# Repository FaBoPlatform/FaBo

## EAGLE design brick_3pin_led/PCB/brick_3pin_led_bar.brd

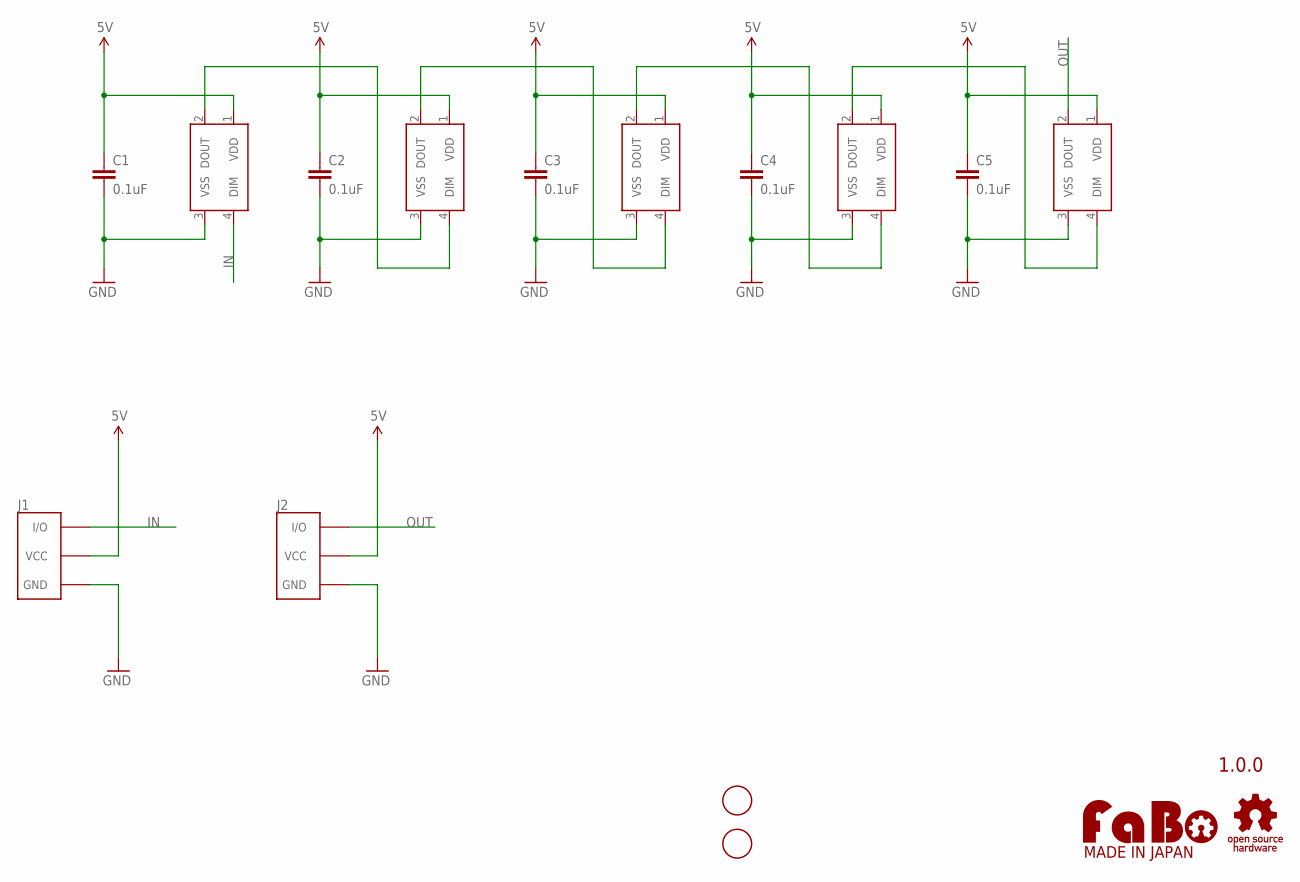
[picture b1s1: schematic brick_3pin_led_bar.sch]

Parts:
C1, C2, C3, C4, C5: 0.1uF; EIA0603
J1, J2: FABO_BRICK_3PIN-CONNECTOR; FABO_BRICK_3PIN_CONNECTOR
LED1, LED2, LED3, LED4, LED5: WS2818B
U$2, U$3: SCREW-PAD-3MM; SCREWPAD_3MM
U$4: LOGO_FABO-S_BOTTOM; LOGO_FABO_S_BOTTOM
U$5: LOGO_OSHW-M_BOTTOM; LOGO_OSHW_M_BOTTOM

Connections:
5V: C1.1, C2.1, C3.1, C4.1, C5.1, J1.VCC, J2.VCC, LED1.1 (VDD), LED2.1 (VDD), LED3.1 (VDD), LED4.1 (VDD), LED5.1 (VDD)
GND: C1.2, C2.2, C3.2, C4.2, C5.2, J1.GND, J2.GND, LED1.3 (VSS), LED2.3 (VSS), LED3.3 (VSS), LED4.3 (VSS), LED5.3 (VSS)
IN: J1.IN/OUT (I/O), LED1.4 (DIM)
unnamed: LED2.2 (DOUT), LED3.4 (DIM)
unnamed: LED3.2 (DOUT), LED4.4 (DIM)
unnamed: LED1.2 (DOUT), LED2.4 (DIM)
unnamed: LED4.2 (DOUT), LED5.4 (DIM)
OUT: J2.IN/OUT (I/O), LED5.2 (DOUT)

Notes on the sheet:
1.0.0

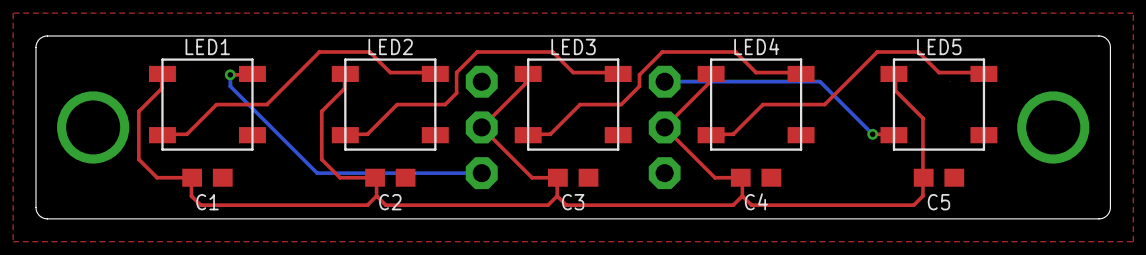
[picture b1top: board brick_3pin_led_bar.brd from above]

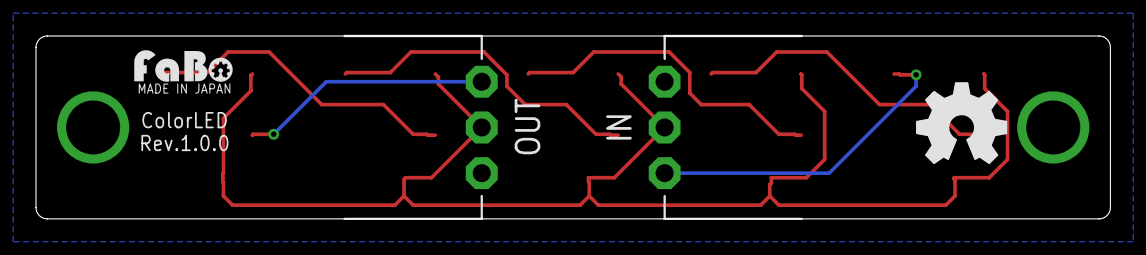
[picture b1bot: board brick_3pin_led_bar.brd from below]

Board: 2 copper layers, 59.7 x 10.2 mm, 16 parts (2 on the bottom side), 8 nets.

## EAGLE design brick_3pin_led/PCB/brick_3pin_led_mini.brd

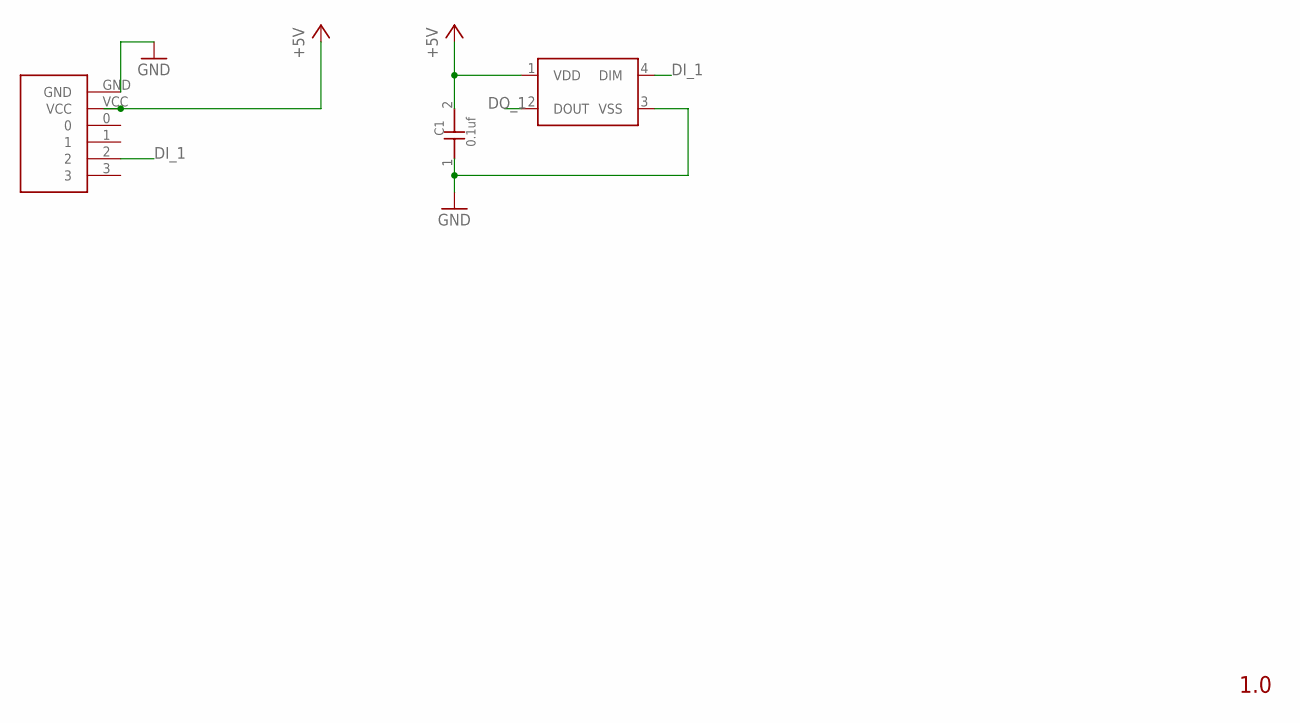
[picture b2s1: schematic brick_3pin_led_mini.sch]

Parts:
C1: 0.1uf; 0603
LED1: WS2818B
U$2: FABO-NANO

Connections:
+5V: C1.2, LED1.1 (VDD), U$2.VCC
DI_1: LED1.4 (DIM), U$2.2
DO_1: LED1.2 (DOUT)
GND: C1.1, LED1.3 (VSS), U$2.GND

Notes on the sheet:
1.0

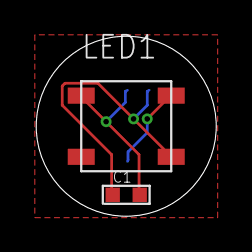
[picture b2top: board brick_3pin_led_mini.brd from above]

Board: 2 copper layers, 10.0 x 10.0 mm, 3 parts (0 on the bottom side), 3 nets.

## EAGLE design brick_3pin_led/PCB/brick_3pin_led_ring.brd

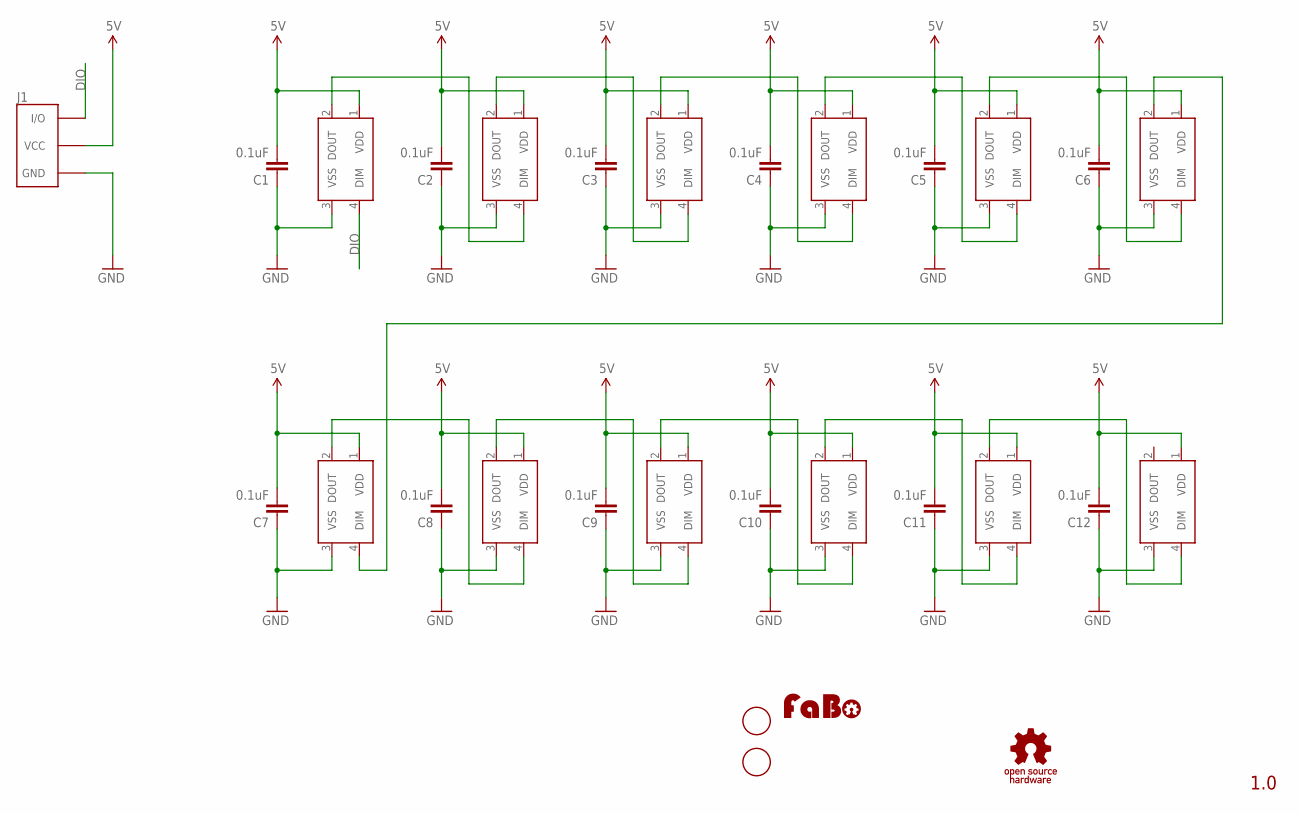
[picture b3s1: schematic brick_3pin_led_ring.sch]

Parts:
C1, C2, C3, C4, C5, C6, C7, C8, C9, C10, C11, C12: 0.1uF; EIA0603
J1: BRICK_3PIN_CONNECTOR
U$2, U$3, U$4, U$5, U$6, U$7, U$8, U$9, U$10, U$11, U$12, U$13: WS2818B
U$14: LOGO_FABO-M; LOGO_FABO_M
U$15: LOGO_OSHW_T-M; LOGO_OSHW_T_M
U$16, U$17: SCREW-PAD-3MM; SCREWPAD_3MM

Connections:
5V: C1.2, C2.2, C3.2, C4.2, C5.2, C6.2, C7.2, C8.2, C9.2, C10.2, C11.2, C12.2, J1.VCC, U$2.1 (VDD), U$3.1 (VDD), U$4.1 (VDD), U$5.1 (VDD), U$6.1 (VDD), U$7.1 (VDD), U$8.1 (VDD), U$9.1 (VDD), U$10.1 (VDD), U$11.1 (VDD), U$12.1 (VDD), U$13.1 (VDD)
DIO: J1.IN/OUT (I/O), U$2.4 (DIM)
GND: C1.1, C2.1, C3.1, C4.1, C5.1, C6.1, C7.1, C8.1, C9.1, C10.1, C11.1, C12.1, J1.GND, U$2.3 (VSS), U$3.3 (VSS), U$4.3 (VSS), U$5.3 (VSS), U$6.3 (VSS), U$7.3 (VSS), U$8.3 (VSS), U$9.3 (VSS), U$10.3 (VSS), U$11.3 (VSS), U$12.3 (VSS), U$13.3 (VSS)
unnamed: U$2.2 (DOUT), U$3.4 (DIM)
unnamed: U$3.2 (DOUT), U$4.4 (DIM)
unnamed: U$4.2 (DOUT), U$5.4 (DIM)
unnamed: U$5.2 (DOUT), U$6.4 (DIM)
unnamed: U$6.2 (DOUT), U$7.4 (DIM)
unnamed: U$7.2 (DOUT), U$8.4 (DIM)
unnamed: U$8.2 (DOUT), U$9.4 (DIM)
unnamed: U$9.2 (DOUT), U$10.4 (DIM)
unnamed: U$10.2 (DOUT), U$11.4 (DIM)
unnamed: U$11.2 (DOUT), U$12.4 (DIM)
unnamed: U$12.2 (DOUT), U$13.4 (DIM)

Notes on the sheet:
1.0

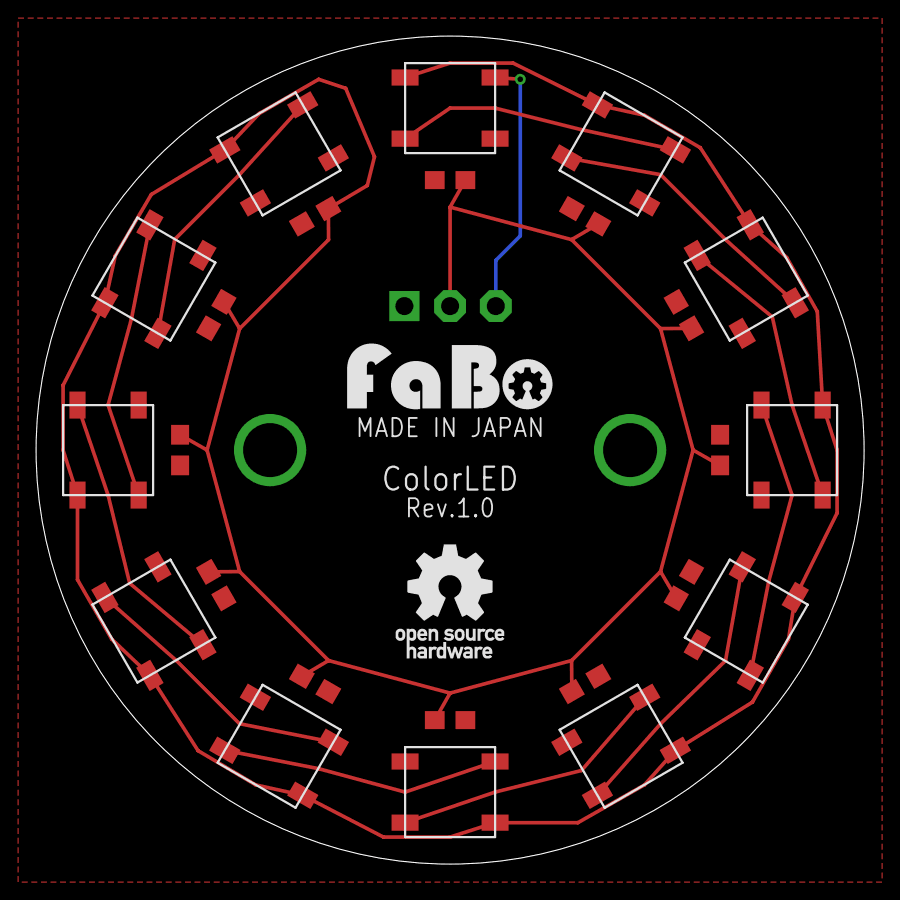
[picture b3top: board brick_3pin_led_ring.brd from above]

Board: 2 copper layers, 46.0 x 46.0 mm, 29 parts (1 on the bottom side), 14 nets.

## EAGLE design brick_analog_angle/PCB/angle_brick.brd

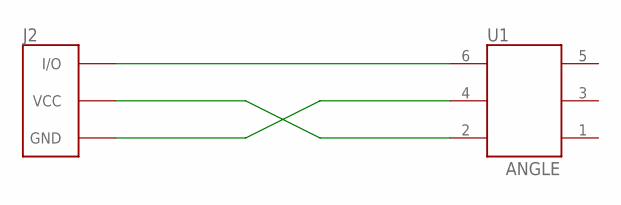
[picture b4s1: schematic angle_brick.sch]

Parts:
J2: BRICK_3PIN
U1: ANGLE; ROTARYENCORDER_BRICK

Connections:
GND: J2.GND, U1.4
unnamed: J2.IN/OUT (I/O), U1.6
VCC: J2.VCC, U1.2

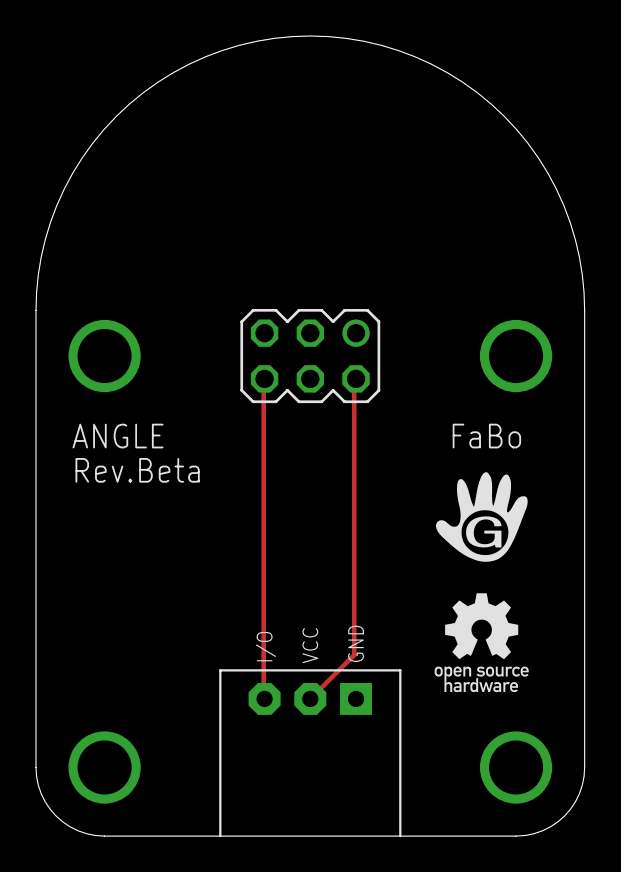
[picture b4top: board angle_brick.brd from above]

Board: 2 copper layers, 30.5 x 44.5 mm, 4 parts (0 on the bottom side), 3 nets.

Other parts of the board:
U$2: LOGO_OSHW_T_M
U$4: LOGO_GCLUE_M

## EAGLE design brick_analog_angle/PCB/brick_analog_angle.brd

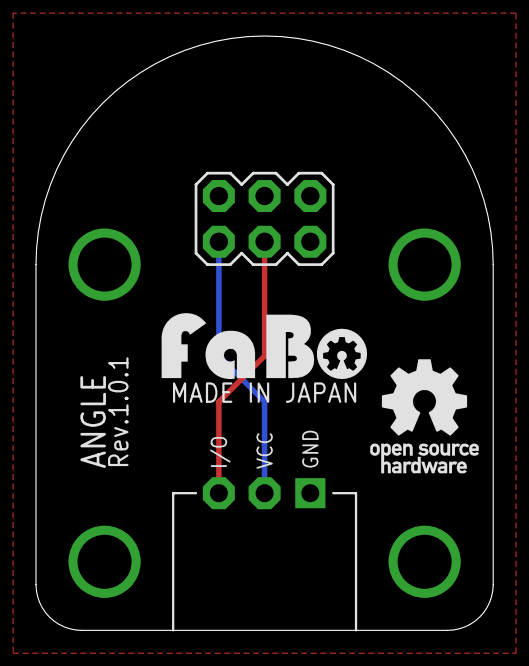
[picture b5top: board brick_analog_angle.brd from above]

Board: 2 copper layers, 25.4 x 33.0 mm, 4 parts (0 on the bottom side), 3 nets.

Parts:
J1: FABO_BRICK_3PIN
U1: ANGLE; ROTARYENCORDER_BRICK
U$2: LOGO_FABO_M
U$3: LOGO_OSHW_T_M

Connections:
GND: J1.GND, U1.5
unnamed: J1.IN/OUT, U1.3
VCC: J1.VCC, U1.1

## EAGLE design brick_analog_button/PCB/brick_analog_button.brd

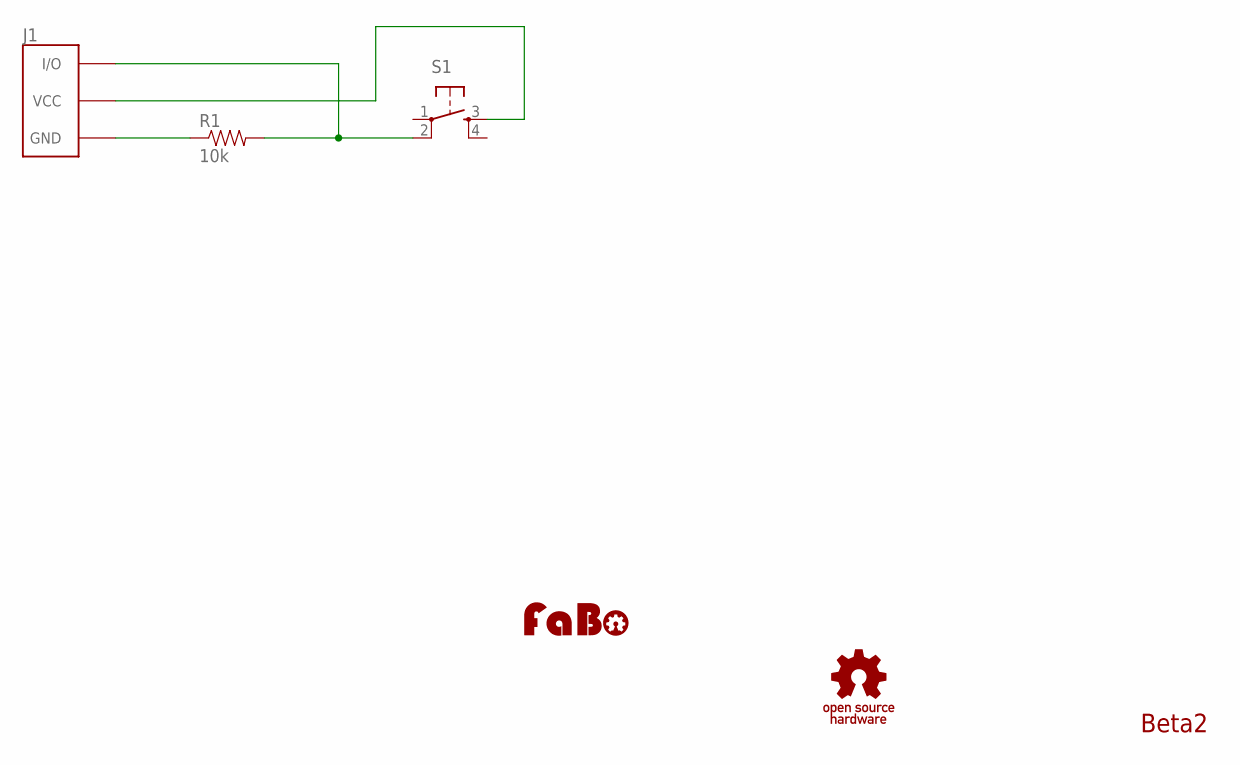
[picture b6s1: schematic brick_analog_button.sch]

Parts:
J1: BRICK_3PIN
R1: 10k; RES-AXL-REGULAR
S1: SWITCH-TACT-6MM; DTS_6_V
U$2: LOGO_FABO-M; LOGO_FABO_M
U$3: LOGO_OSHW_T-M; LOGO_OSHW_T_M

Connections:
GND: J1.GND, R1.P$1 (1)
unnamed: J1.VCC, S1.3
unnamed: J1.IN/OUT (I/O), R1.P$2 (2), S1.2

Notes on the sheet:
Beta2

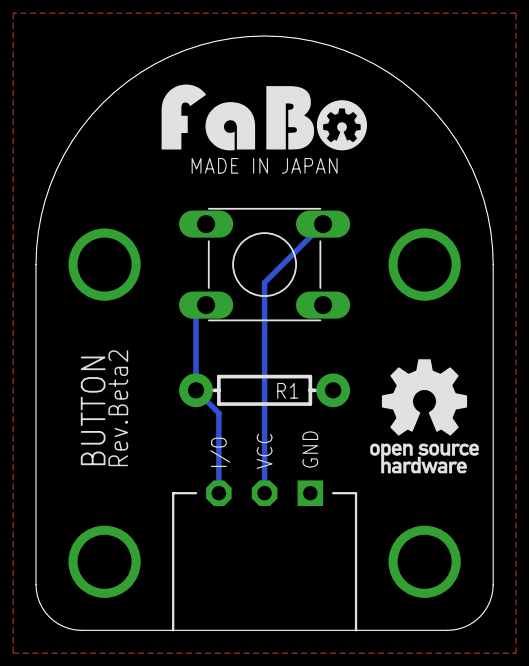
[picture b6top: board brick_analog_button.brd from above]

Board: 2 copper layers, 25.4 x 33.0 mm, 5 parts (0 on the bottom side), 3 nets.

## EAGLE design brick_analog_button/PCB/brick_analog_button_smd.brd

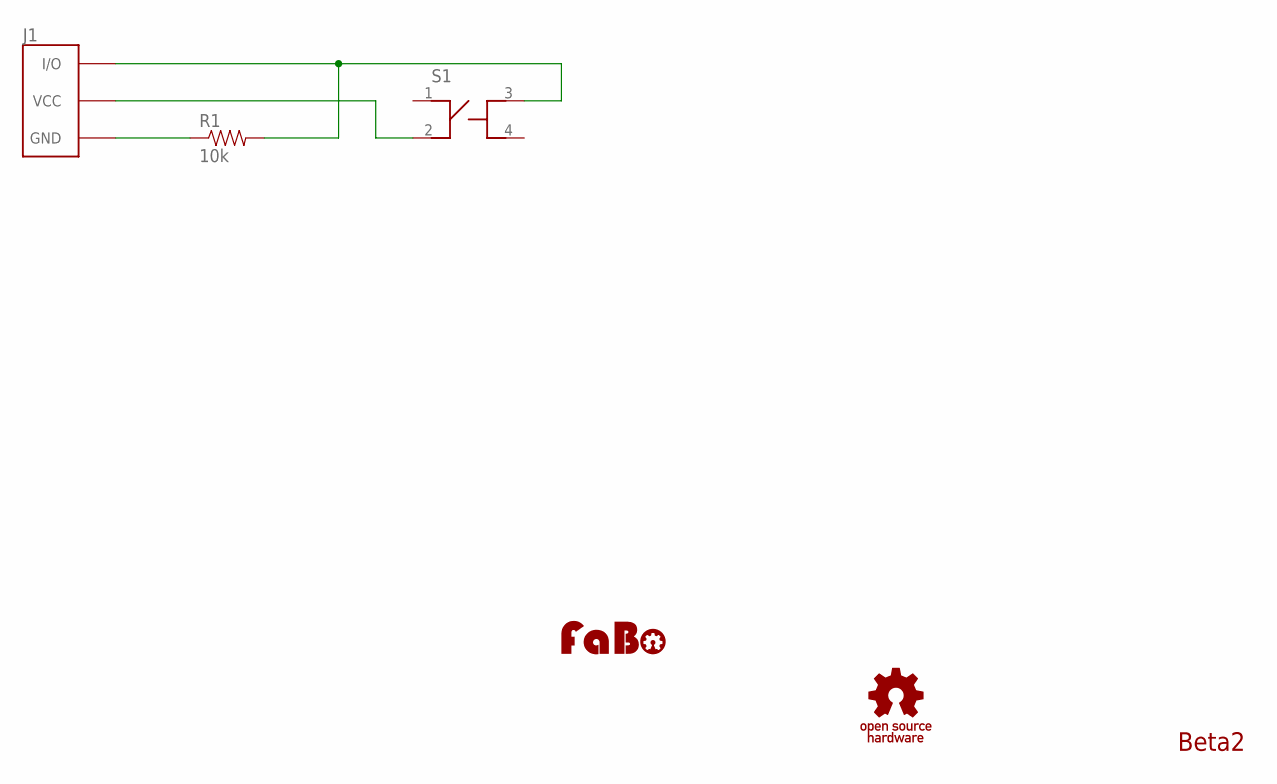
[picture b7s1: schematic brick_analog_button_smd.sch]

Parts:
J1: BRICK_3PIN
R1: 10k; 0603-RES
S1: SWITCH-LS6J2M-T
U$1: LOGO_FABO-M; LOGO_FABO_M
U$4: LOGO_OSHW_T-M; LOGO_OSHW_T_M

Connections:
GND: J1.GND, R1.1
unnamed: J1.VCC, S1.2
unnamed: J1.IN/OUT (I/O), R1.2, S1.3

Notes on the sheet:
Beta2

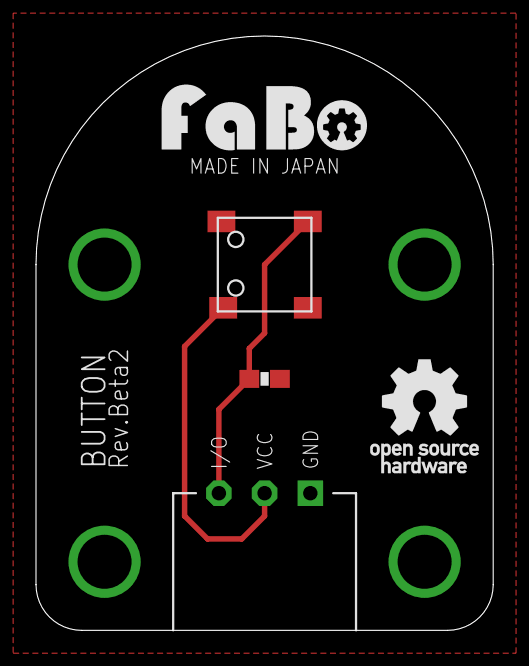
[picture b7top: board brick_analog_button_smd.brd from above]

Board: 2 copper layers, 25.4 x 33.0 mm, 5 parts (0 on the bottom side), 3 nets.

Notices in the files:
parts and their libraries:
FaBo-etc: Released under the Creative Commons Attribution-ShareAlike 4.0 License
https://creativecommons.org/licenses/by-sa/4.0
FaBo-etc: Released under the Creative Commons
SparkFun-Resistors: Licensing: Creative Commons ShareAlike 4.0 International - https://creativecommons.org/licenses/by-sa/4.0
